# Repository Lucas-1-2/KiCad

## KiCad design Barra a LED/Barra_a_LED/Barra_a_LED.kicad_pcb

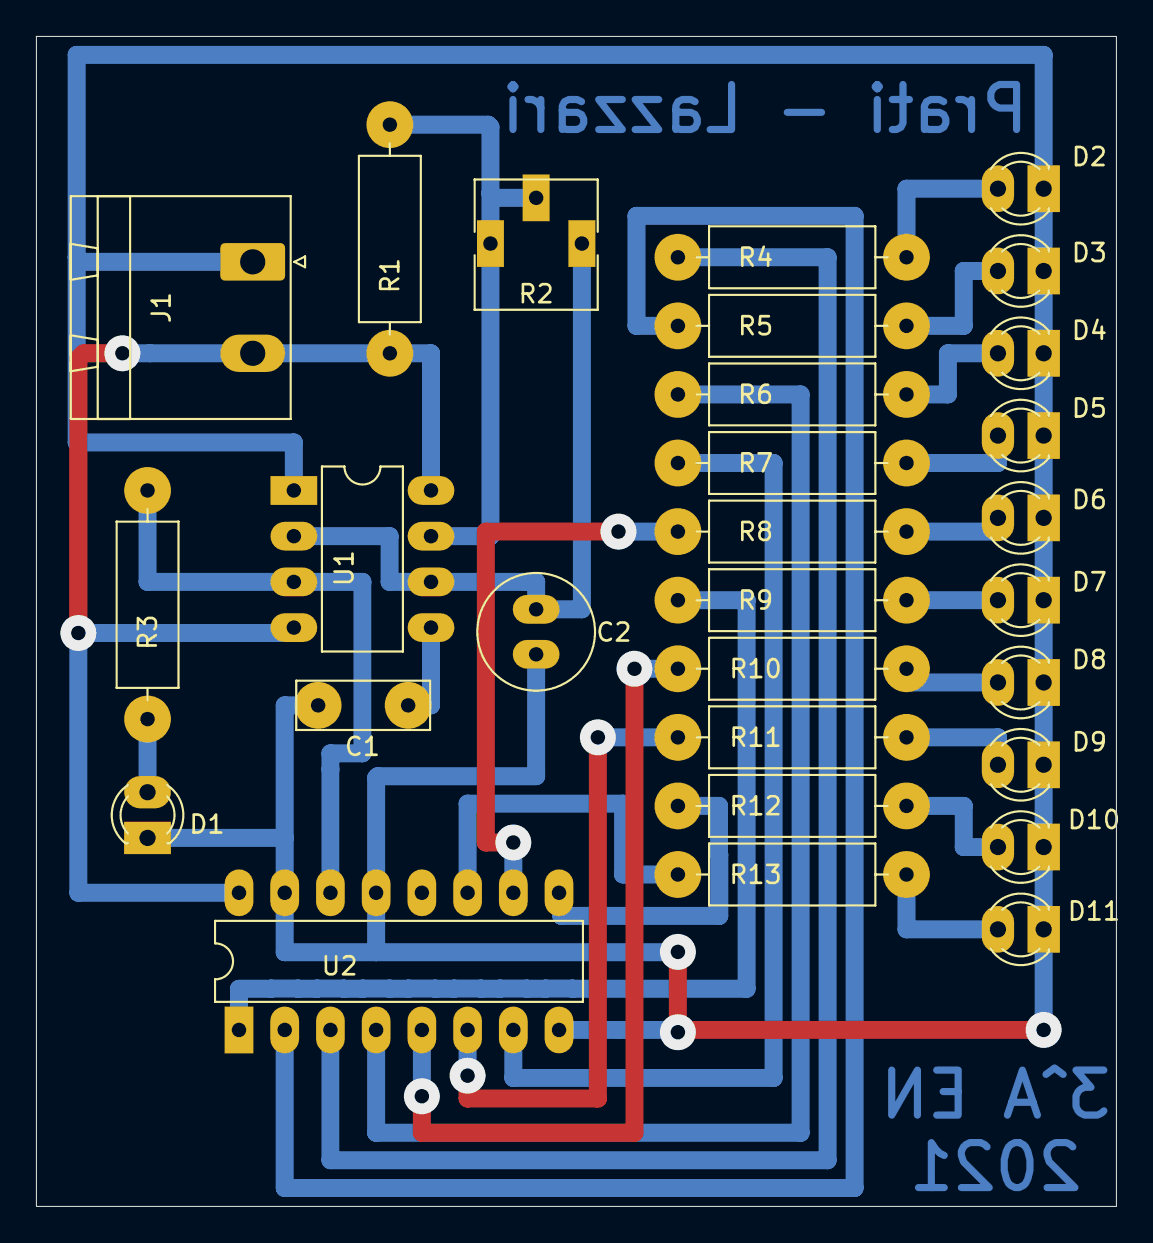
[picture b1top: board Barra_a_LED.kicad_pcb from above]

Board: 2 copper layers, 60.0 x 65.0 mm, 29 parts (0 on the bottom side), 27 nets.

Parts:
C1: 10nF pol.; C_Rect_L7.2mm_W2.5mm_P5.00mm_FKS2_FKP2_MKS2_MKP2
C2: 10 uF elettr.; C_Radial_D6.3mm_H5.0mm_P2.50mm
D1: LED V; LED_D3.0mm
D2, D3, D4, D5, D6, D7, D8, D9, D10, D11: R; LED_D3.0mm
J1: Conn_01x02_Male; PhoenixContact_MSTBA_2,5_2-G-5,08_1x02_P5.08mm_Horizontal
R1: 10K; R_Axial_DIN0309_L9.0mm_D3.2mm_P12.70mm_Horizontal
R2: R_POT_10K; Potentiometer_Vishay_T73YP_Vertical
R3: 1K; R_Axial_DIN0309_L9.0mm_D3.2mm_P12.70mm_Horizontal
R4, R5, R6, R7, R8, R9, R10, R11, R12, R13: 150; R_Axial_DIN0309_L9.0mm_D3.2mm_P12.70mm_Horizontal
U1: NE555P; DIP-8_W7.62mm_LongPads
U2: 4017; DIP-16_W7.62mm_LongPads

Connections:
GND: C1.2, C2.2, D1.1, D2.1, D3.1, D4.1, D5.1, D6.1, D7.1, D8.1, D9.1, D10.1, D11.1, J1.1, U1.1, U2.8, U2.13, U2.15
unnamed: C1.1, U1.5
unnamed: C2.1, R2.1, U1.2, U1.6
unnamed: D1.2, R3.1
unnamed: D2.2, R4.2
unnamed: D3.2, R5.2
unnamed: D4.2, R6.2
unnamed: D5.2, R7.2
unnamed: D6.2, R8.2
unnamed: D7.2, R9.2
unnamed: D8.2, R10.2
unnamed: D9.2, R11.2
unnamed: D10.2, R12.2
unnamed: D11.2, R13.2
unnamed: R1.2, R2.2, R2.3, U1.7
unnamed: R3.2, U1.3, U2.14
unnamed: R4.1, U2.3
unnamed: R5.1, U2.2
unnamed: R6.1, U2.4
unnamed: R7.1, U2.7
unnamed: R8.1, U2.10
unnamed: R9.1, U2.1
unnamed: R10.1, U2.5
unnamed: R11.1, U2.6
unnamed: R12.1, U2.9
unnamed: R13.1, U2.11
VCC: J1.2, R1.1, U1.4, U1.8, U2.16

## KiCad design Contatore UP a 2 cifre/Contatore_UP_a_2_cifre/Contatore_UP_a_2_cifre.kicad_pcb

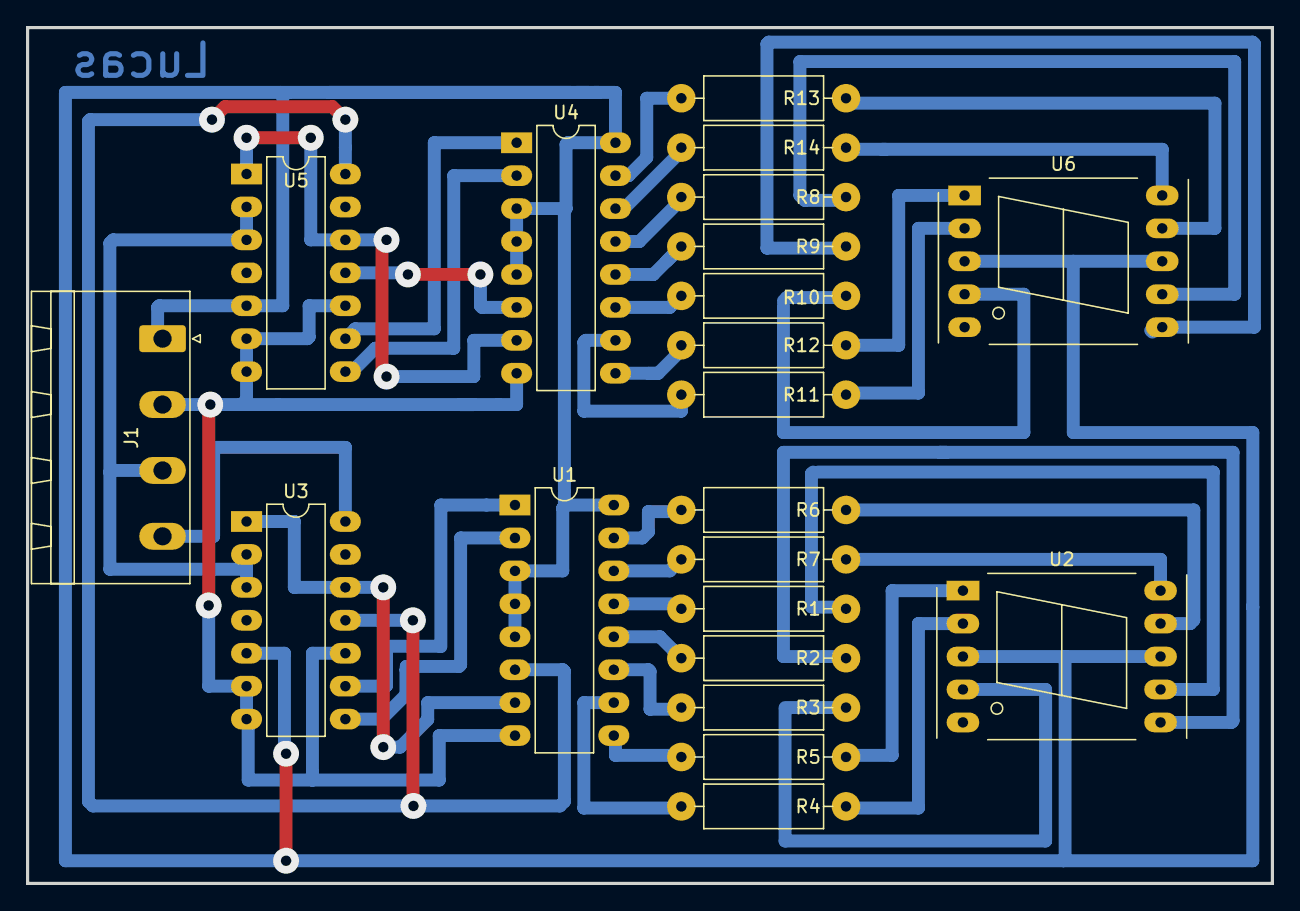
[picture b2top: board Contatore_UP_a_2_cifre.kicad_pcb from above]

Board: 2 copper layers, 96.0 x 66.0 mm, 21 parts (0 on the bottom side), 40 nets.

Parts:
J1: Conn_01x04_Female; PhoenixContact_MSTBA_2,5_4-G-5,08_1x04_P5.08mm_Horizontal
R1, R2, R3, R4, R5, R6, R7, R8, R9, R10, R11, R12, R13, R14: R 330; R_Axial_DIN0309_L9.0mm_D3.2mm_P12.70mm_Horizontal
U1, U4: 74LS47; DIP-16_W7.62mm_LongPads
U2, U6: KCSA02-105; 7SegmentLED_LTS6760_LTS6780
U3, U5: 74LS90; DIP-14_W7.62mm_LongPads

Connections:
GND: J1.2, U1.8, U3.6, U3.7, U3.10, U4.8, U5.6, U5.7, U5.10
unnamed: R1.1, U2.7
unnamed: R1.2, U1.13
unnamed: R2.1, U2.6
unnamed: R2.2, U1.12
unnamed: R3.1, U2.4
unnamed: R3.2, U1.11
unnamed: R4.1, U2.2
unnamed: R4.2, U1.10
unnamed: R5.1, U2.1
unnamed: R5.2, U1.9
unnamed: R6.1, U2.9
unnamed: R6.2, U1.15
unnamed: R7.1, U2.10
unnamed: R7.2, U1.14
unnamed: R8.1, U6.7
unnamed: R8.2, U4.13
unnamed: R9.1, U6.6
unnamed: R9.2, U4.12
unnamed: R10.1, U6.4
unnamed: R10.2, U4.11
unnamed: R11.1, U6.2
unnamed: R11.2, U4.10
unnamed: R12.1, U6.1
unnamed: R12.2, U4.9
unnamed: R13.1, U6.9
unnamed: R13.2, U4.15
unnamed: R14.1, U6.10
unnamed: R14.2, U4.14
unnamed: U1.1, U3.9
unnamed: U1.2, U3.8
unnamed: U1.6, U3.11, U5.14
unnamed: U1.7, U3.1, U3.12
unnamed: U4.1, U5.9
unnamed: U4.2, U5.8
unnamed: U4.6, U5.11
unnamed: U4.7, U5.1, U5.12
Reset: J1.3, U3.2, U3.3, U5.2, U5.3
Vcc: J1.1, U1.3, U1.4, U1.5, U1.16, U2.3, U2.8, U3.5, U4.3, U4.4, U4.5, U4.16, U5.5, U6.3, U6.8
Vin: J1.4, U3.14

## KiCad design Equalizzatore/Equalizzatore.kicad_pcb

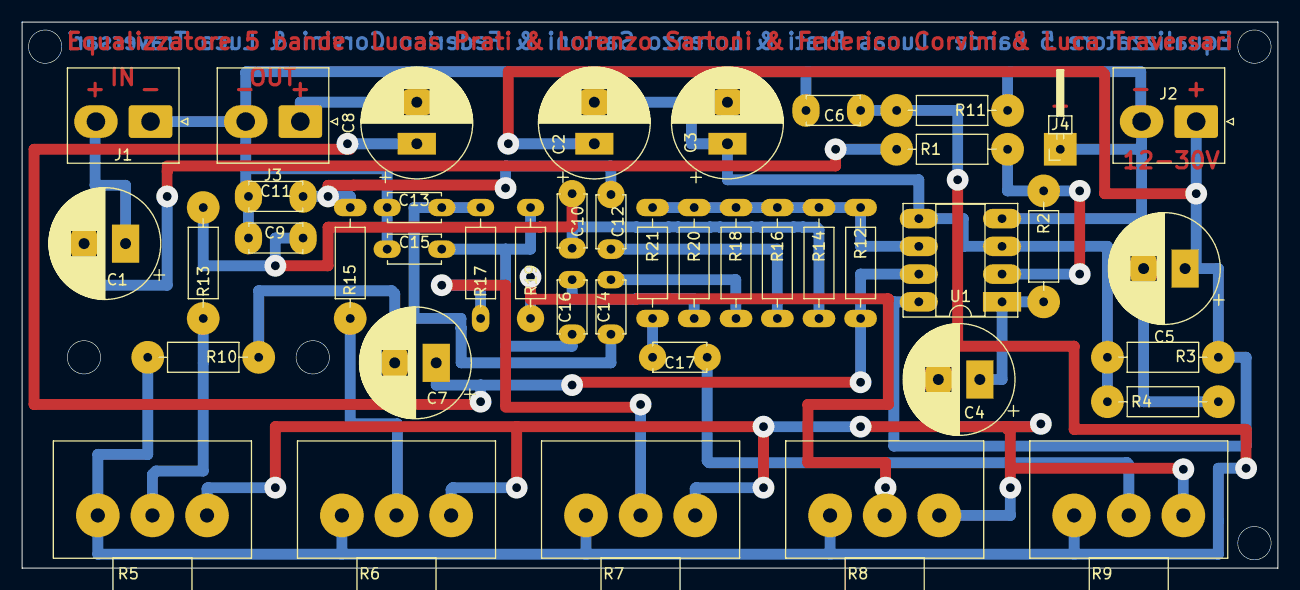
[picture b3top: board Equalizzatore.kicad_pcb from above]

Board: 2 copper layers, 115.0 x 50.0 mm, 43 parts (0 on the bottom side), 27 nets.

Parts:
C1, C2, C3, C4, C8: 100uF; CP_Radial_D10.0mm_P3.80mm
C5: 1000uF; CP_Radial_D10.0mm_P3.80mm
C6, C15, C16, C17: 1nF; C_Disc_D4.7mm_W2.5mm_P5.00mm
C7: 470uF; CP_Radial_D10.0mm_P3.80mm
C9: 47nF; C_Disc_D4.7mm_W2.5mm_P5.00mm
C10: 470nF; C_Disc_D4.7mm_W2.5mm_P5.00mm
C11, C12: 15nF; C_Disc_D4.7mm_W2.5mm_P5.00mm
C13, C14: 4.7nF; C_Disc_D4.7mm_W2.5mm_P5.00mm
J1: Audio IN; JST_NV_B02P-NV_1x02_P5.00mm_Vertical
J2: VDD stab. 12-30V; JST_NV_B02P-NV_1x02_P5.00mm_Vertical
J3: AUDIO OUT; JST_NV_B02P-NV_1x02_P5.00mm_Vertical
J4: GND ausiliario; PinHeader_1x01_P2.00mm_Horizontal
R1, R3, R4: 47k; R_Axial_DIN0207_L6.3mm_D2.5mm_P10.16mm_Horizontal
R2: 100k; R_Axial_DIN0207_L6.3mm_D2.5mm_P10.16mm_Horizontal
R5, R6, R7, R8, R9: 22k; Potentiometer_Alps_RK163_Single_Horizontal
R10, R11: 4.7k; R_Axial_DIN0207_L6.3mm_D2.5mm_P10.16mm_Horizontal
R12: 220k; R_Axial_DIN0207_L6.3mm_D2.5mm_P10.16mm_Horizontal
R13, R14, R15, R16, R17, R18, R19, R20: 33k; R_Axial_DIN0207_L6.3mm_D2.5mm_P10.16mm_Horizontal
R21: 56k; R_Axial_DIN0207_L6.3mm_D2.5mm_P10.16mm_Horizontal
U1: NE5532; DIP-8_W7.62mm_Socket_LongPads

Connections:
GND: C3.2, C5.2, C6.2, C9.1, C11.1, C13.1, C15.1, J1.1, J2.2, J3.2, J4.1, R4.2, R11.1, U1.4 (V-)
unnamed: C1.1, J1.2
unnamed: C1.2, R1.1
unnamed: C2.2, C3.1, R3.2, R4.1, U1.3 (+), U1.5 (+)
unnamed: C4.1, R2.2, U1.1
unnamed: C4.2, R5.3, R6.3, R7.3, R8.3, R9.3
unnamed: C6.1, R5.1, R6.1, R7.1, R8.1, R9.1, R10.2, R11.2
unnamed: C7.1, C8.1, R12.2, U1.7
unnamed: C7.2, R10.1
unnamed: C8.2, J3.1
unnamed: C9.2, C10.1, R13.2
unnamed: C10.2, R14.1
unnamed: C11.2, C12.1, R15.2
unnamed: C12.2, R16.1
unnamed: C13.2, C14.1, R17.2
unnamed: C14.2, R18.1
unnamed: C15.2, C16.1, R19.2
unnamed: C16.2, R20.1
unnamed: C17.1, R9.2
unnamed: C17.2, R21.1
unnamed: R1.2, R2.1, U1.2 (-)
unnamed: R12.1, R14.2, R16.2, R18.2, R20.2, R21.2, U1.6 (-)
unnamed: R5.2, R13.1
unnamed: R6.2, R15.1
unnamed: R7.2, R17.1
unnamed: R8.2, R19.1
VDD: C2.1, C5.1, J2.1, R3.1, U1.8 (V+)
